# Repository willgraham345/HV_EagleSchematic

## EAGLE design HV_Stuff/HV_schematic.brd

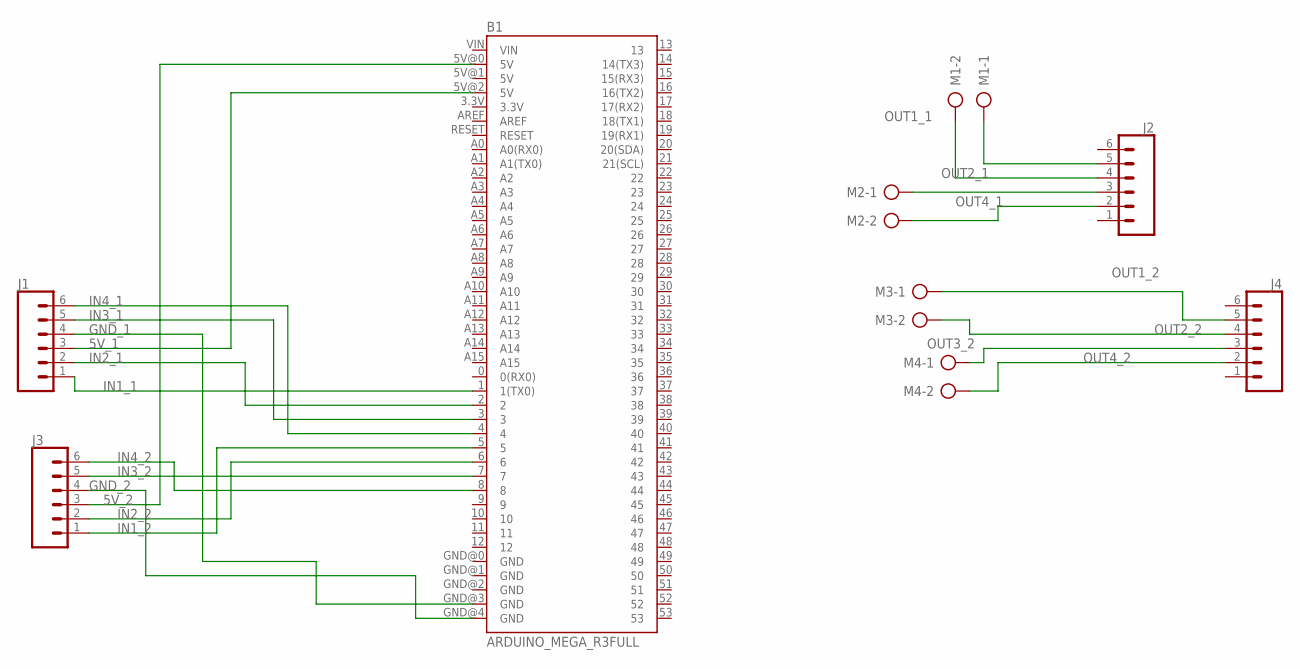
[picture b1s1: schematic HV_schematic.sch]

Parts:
B1: ARDUINO_MEGA_R3FULL; ARDUINO_MEGA
J1, J2, J3, J4: CONN_06LONGPADS; 1X06_LONGPADS
M1, M2, M3, M4: AK500/2

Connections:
5V_1: B1.5V@2 (5V), J1.3
5V_2: B1.5V@0 (5V), J3.3
GND_1: B1.GND@3 (GND), J1.4
GND_2: B1.GND@4 (GND), J3.4
IN1_1: B1.1 (1(TX0)), J1.1
IN1_2: B1.5, J3.1
IN2_1: B1.2, J1.2
IN2_2: B1.6, J3.2
IN3_1: B1.3, J1.5
IN3_2: B1.7, J3.5
IN4_1: B1.4, J1.6
IN4_2: B1.8, J3.6
unnamed: J2.3, M2.1
OUT1_1: J2.5, M1.1
OUT1_2: J4.5, M3.1
OUT2_1: J2.4, M1.2
OUT2_2: J4.4, M3.2
OUT3_2: J4.3, M4.1
OUT4_1: J2.2, M2.2
OUT4_2: J4.2, M4.2

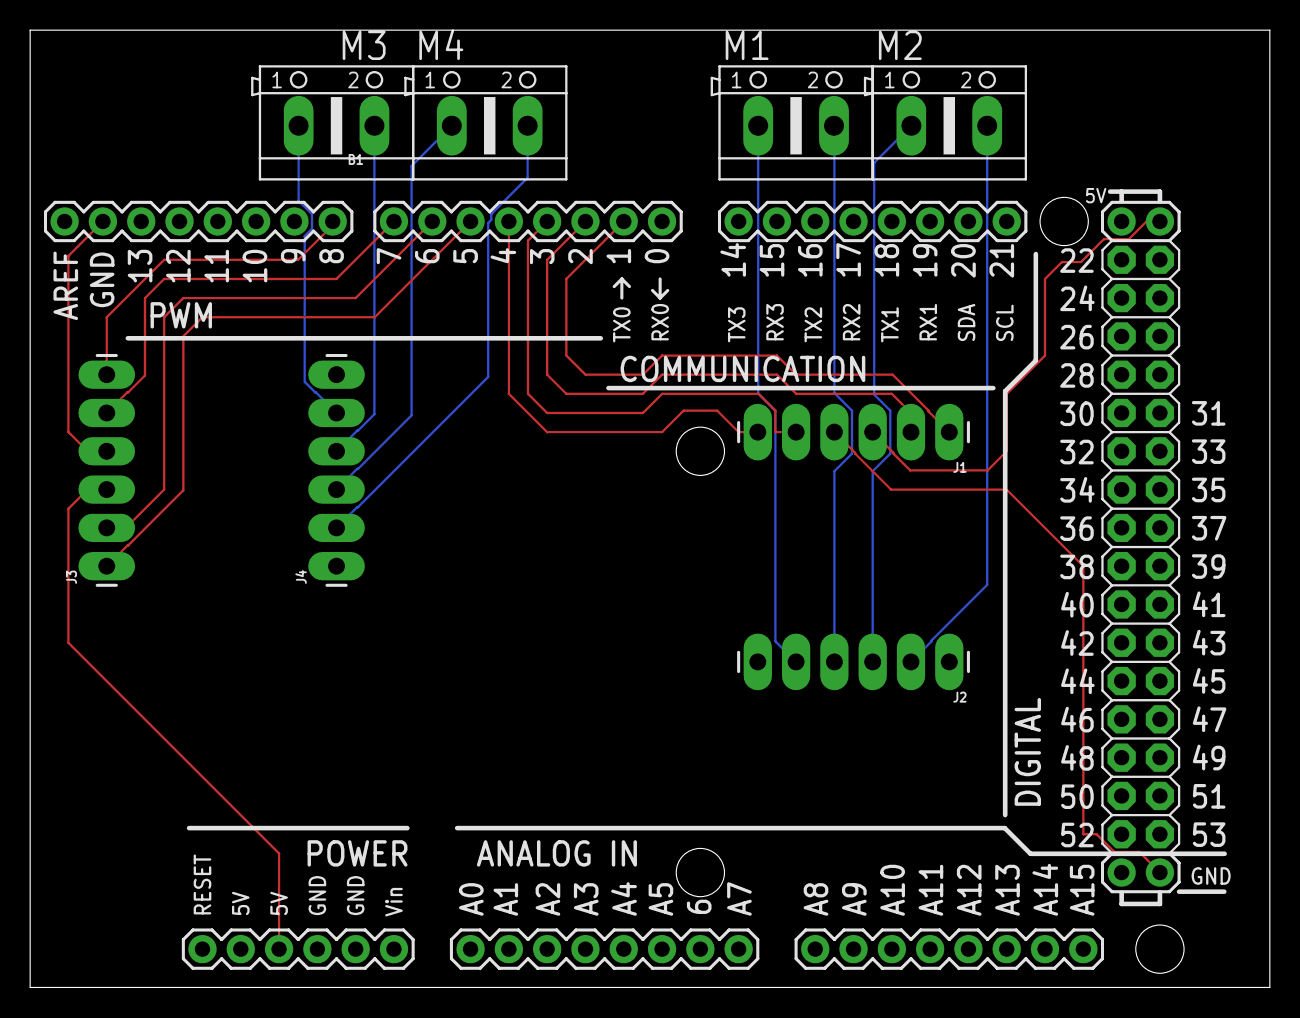
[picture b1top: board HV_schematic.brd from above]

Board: 2 copper layers, 82.2 x 63.5 mm, 9 parts (0 on the bottom side), 20 nets.

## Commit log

2022-09-01 Initial creation of HV schematic, only the frame
    Don't have necessary libraries, and EAGLE is offline. Need to reinstall EAGLE to make this work.
2022-09-01 Made basic schematic with Arduino board included
    Next step is designing PCB
2022-09-06 PCB design 1 made
    Looks pretty :)
2022-09-08 Changed to mega
    Got schematic and PCB running on a mega
2022-09-08 Made it, it's gorgeous. It looks very pretty

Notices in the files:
parts and their libraries:
SparkFun-Connectors: Licensing: Creative Commons ShareAlike 4.0 International - https://creativecommons.org/licenses/by-sa/4.0
